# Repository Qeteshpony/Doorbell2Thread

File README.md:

# Doorbell2Thread

### Turning an old analog doorbell into a smart one... 

[Hardware Documentation](https://qeteshpony.github.io/Doorbell2Thread)

# Hardware description

This is a very simple device that can be connected to an old analog intercom system to notify home assistant about someone ringing the bell. This was specifically made for the system in the house I live in but it might be compatible with yours as well - no guarantees though. 

I am using a small form factor ESP32-H2 module (Waveshare ESP32-H2 Mini) because the H2 is low power and the power supply for the intercom can't handle much current. 

There's also some protective circuitry since my first prototype got completely fried by induced voltages in the intercom cables. This version now runs stable and without problems. 

# Software

This is running on ESPHome. My configuration is available in this repo, see [doorbell.yaml](doorbell.yaml) (You of course have to add your secrets before using it...) 

This configuration is using the built in RGB led on the ESP-module to show the status. It's brightness can be tuned through Home Assistant to make it visible through the case if desired.

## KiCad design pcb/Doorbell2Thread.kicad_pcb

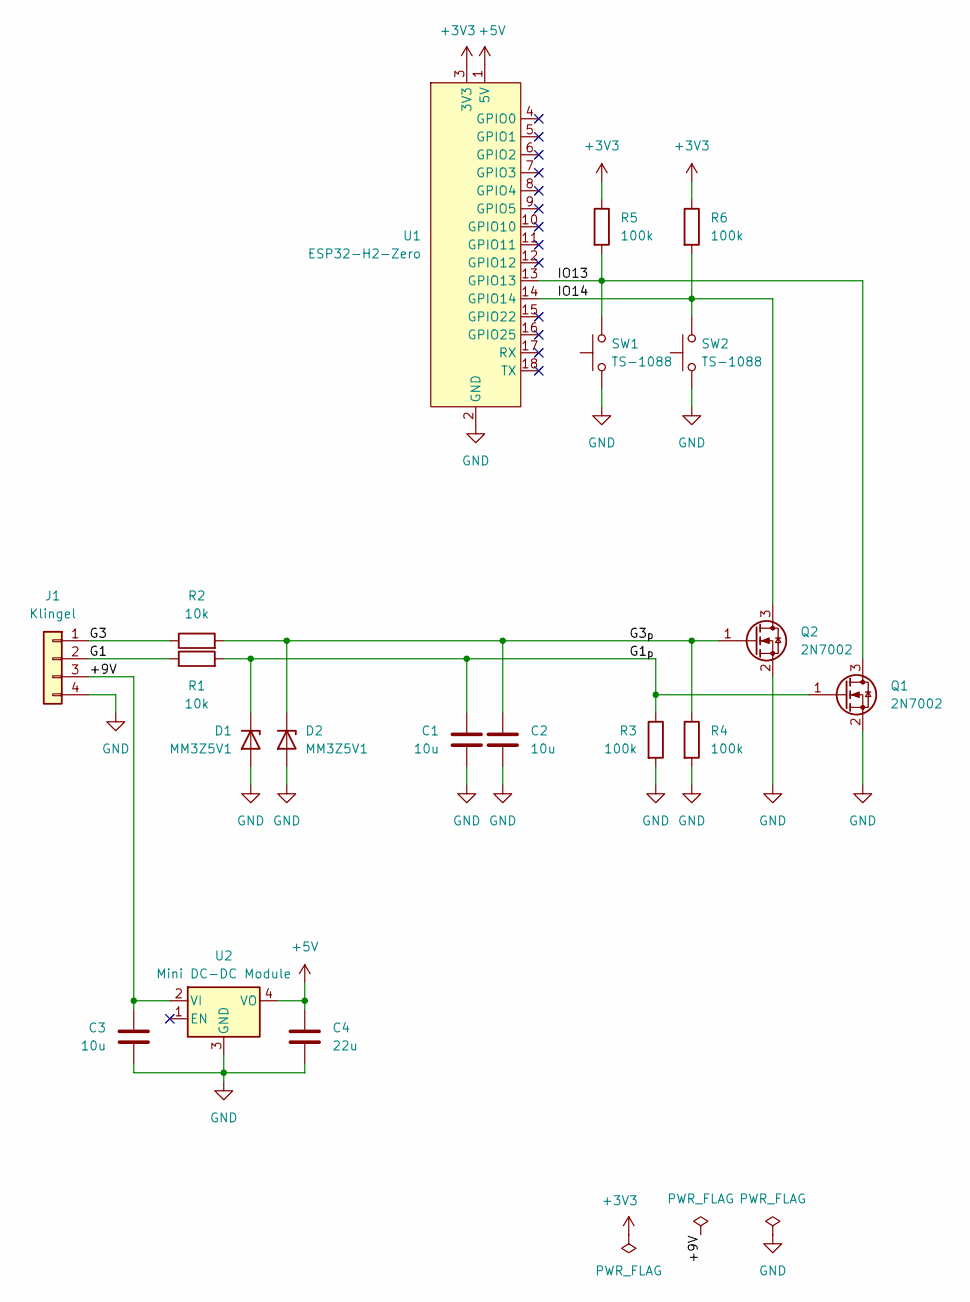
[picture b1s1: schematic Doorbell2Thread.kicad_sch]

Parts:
C1, C2: 10u; C_0603_1608Metric; LCSC C19702
C3: 10u; C_0805_2012Metric; LCSC C440198
C4: 22u; C_0805_2012Metric; LCSC C45783
D1, D2: MM3Z5V1; D_SOD-323; LCSC C19077455
J1: Klingel; JST_PH_S4B-PH-K_1x04_P2.00mm_Horizontal
Q1, Q2: 2N7002; SOT-23; LCSC C8545
R1, R2: 10k; R_0402_1005Metric; LCSC C25744
R3, R4, R5, R6: 100k; R_0402_1005Metric; LCSC C25741
SW1, SW2: TS-1088; SW_Push_SPST_NO_Alps_SKRK; LCSC C720477
U1: ESP32-H2-Zero
U2: Mini DC-DC Module

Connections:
+3V3: R5.1, R6.1, U1.3 (3V3)
+5V: C4.1, U1.1 (5V), U2.4 (VO)
/+9V: C3.1, J1.3, U2.2 (VI)
/G1: J1.2, R1.1
/G1_{p}: C1.1, D1.1 (K), Q1.1 (G), R1.2, R3.1
/G3: J1.1, R2.1
/G3_{p}: C2.1, D2.1 (K), Q2.1 (G), R2.2, R4.1
/IO13: Q1.3 (D), R5.2, SW1.2, U1.13 (GPIO13)
/IO14: Q2.3 (D), R6.2, SW2.2, U1.14 (GPIO14)
GND: C1.2, C2.2, C3.2, C4.2, D1.2 (A), D2.2 (A), J1.4, Q1.2 (S), Q2.2 (S), R3.2, R4.2, SW1.1, SW2.1, U1.2 (GND), U2.3 (GND)

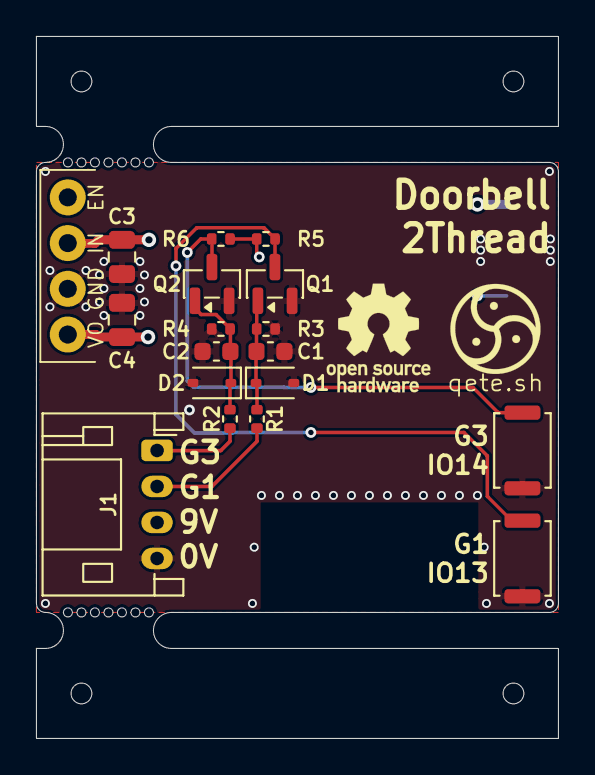
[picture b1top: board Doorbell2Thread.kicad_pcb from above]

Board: 4 copper layers, 29.0 x 39.0 mm, 21 parts (1 on the bottom side), 10 nets.

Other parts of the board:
mouse-bite-2mm-slot, mouse-bite-2mm-slot#2: VAL**; mouse-bite-2x5mm-slot-onesided-v2

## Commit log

2025-12-07 feat: initial commit
2026-06-28 fix: add protection circuitry
    The doorbell was killing the mosfets on the board so some protection was needed
    feat: replaced the expensive LME78
    This caused a major redesign of the whole board
    fix: update to KiCad 10
2026-06-28 chore: cleanup
2026-06-28 feat: add yaml for ESPHome
2026-06-28 docs: add hw and sw description
2026-06-28 chore(main): release 1.0.0
